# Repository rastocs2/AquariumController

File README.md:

AquariumController
==================

Aquarium controller based on Arduino and 4D Systems Intelligent Display Module.

## Components

1. Arduino Mega 2560 R3 (http://arduino.cc/en/Main/ArduinoBoardMega2560)
2. 4D Systems µLCD-28PTU (http://www.4dsystems.com.au/product/1/8/4D_Intelligent_Display_Modules/uLCD_28PTU/)
3. Real Time Clock Module DS3231 - it is much more accurate than DS1307 (http://www.ebay.com/sch/i.html?_trksid=p2050601.m570.l1313.TR0.TRC0.XDS3231+AT24C32&_nkw=DS3231+AT24C32&_sacat=0&_from=R40)
4. 8 Channel 5V Opto-Isolated Relay Module Shield (http://www.ebay.com/sch/i.html?_odkw=8+Channel+5V+Relay+Module&_osacat=0&_from=R40&_trksid=p2045573.m570.l1311.R1.TR3.TRC2.A0&_nkw=8+channel+5v+relay+module&_sacat=0)
5. Digital Temperature Sensor DS18B20 (http://www.ebay.com/sch/i.html?_odkw=DS18B20+Waterproof&_osacat=0&_from=R40&_trksid=p2045573.m570.l1311.R1.TR2.TRC1.A0.XDS18B20+aterproof&_nkw=ds18b20+waterproof&_sacat=0)
6. pH module based on LMP91200 (http://www.ti.com/product/lmp91200)
7. ORP module based on LMP91200 (http://www.ti.com/product/lmp91200)
8. WiFi module based on CC3000 (http://www.ti.com/product/cc3000) - will finished in version 3.0

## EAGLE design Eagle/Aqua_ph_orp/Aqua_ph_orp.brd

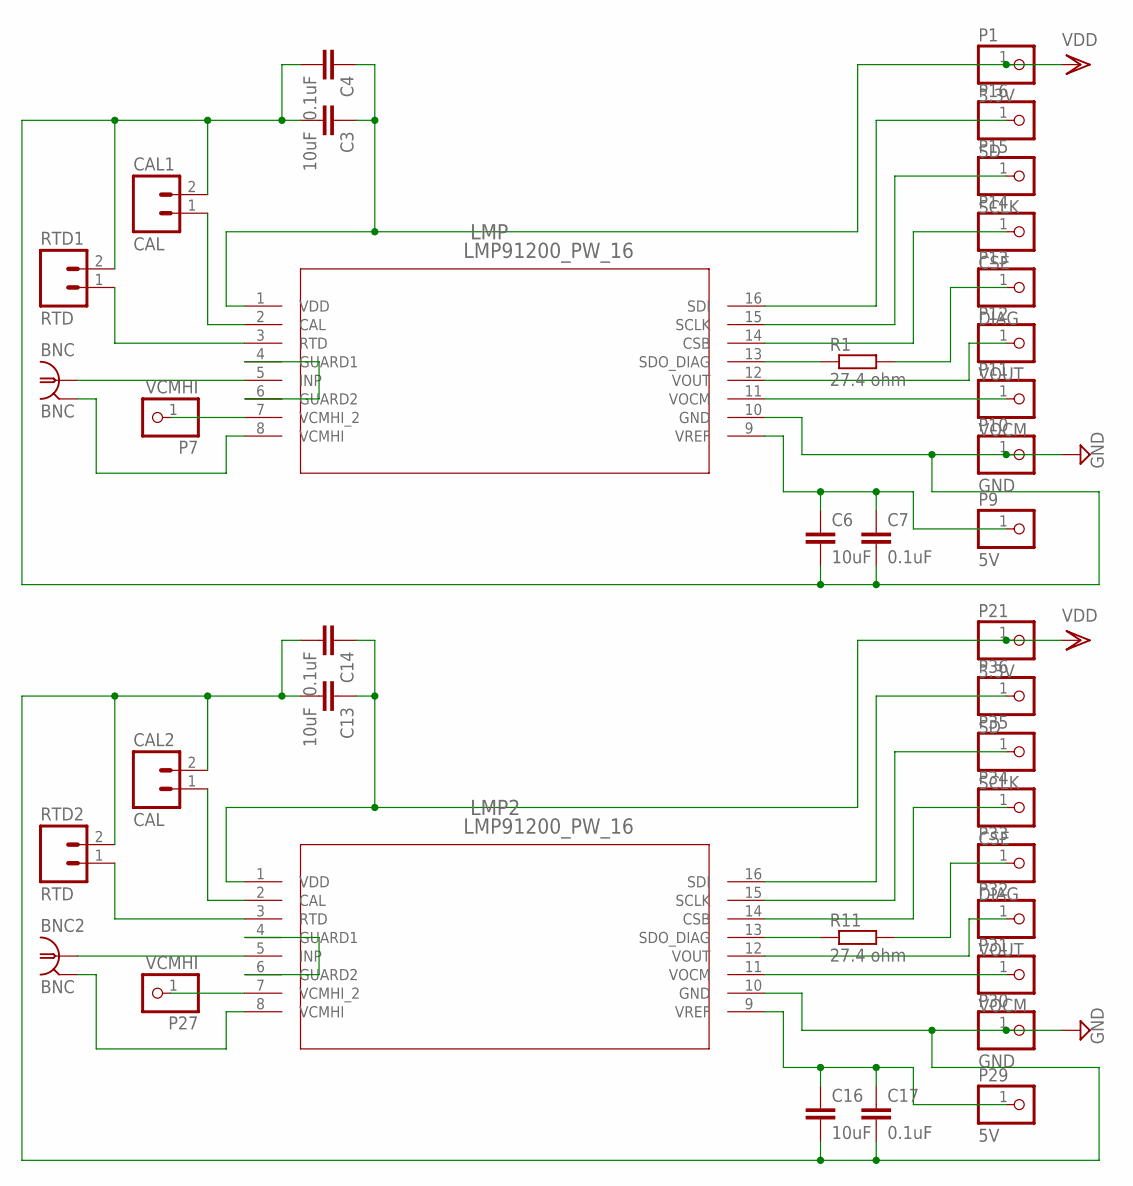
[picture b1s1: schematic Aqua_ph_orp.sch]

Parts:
BNC, BNC2: BNC; AMP_227161
C3, C6, C13, C16: 10uF; C3216
C4, C14: 0.1uF; C0603
C7, C17: 0.1uF; C1206
CAL1, CAL2: CAL; SCREWTERMINAL-KF-301-2P
LMP, LMP2: LMP91200_PW_16; MTC16
P1, P21: 3.3V; 1X01
P7, P27: VCMHI; 1X01
P9, P29: 5V; 1X01
P10, P30: GND; 1X01
P11, P31: VOCM; 1X01
P12, P32: VOUT; 1X01
P13, P33: DIAG; 1X01
P14, P34: CSE; 1X01
P15, P35: SCLK; 1X01
P16, P36: SD; 1X01
R1, R11: 27.4 ohm; R0603
RTD1, RTD2: RTD; SCREWTERMINAL-KF-301-2P

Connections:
GND: C3.2, C4.2, C6.2, C7.2, C13.2, C14.2, C16.2, C17.2, CAL1.2, CAL2.2, LMP.10 (GND), LMP2.10 (GND), P10.1, P30.1, RTD1.2, RTD2.2
unnamed: LMP.7 (VCMHI_2), P7.1
unnamed: BNC.2 (GND), LMP.8 (VCMHI)
unnamed: LMP.4 (GUARD1), LMP.6 (GUARD2)
unnamed: CAL1.1, LMP.2 (CAL)
unnamed: LMP.3 (RTD), RTD1.1
unnamed: C6.1, C7.1, LMP.9 (VREF), P9.1
unnamed: LMP2.14 (CSB), P34.1
unnamed: LMP2.15 (SCLK), P35.1
unnamed: LMP2.16 (SDI), P36.1
unnamed: LMP2.12 (VOUT), P32.1
unnamed: P33.1, R11.2
unnamed: LMP2.11 (VOCM), P31.1
unnamed: LMP2.13 (SDO_DIAG), R11.1
unnamed: BNC2.1, LMP2.5 (INP)
unnamed: LMP2.7 (VCMHI_2), P27.1
unnamed: BNC2.2 (GND), LMP2.8 (VCMHI)
unnamed: LMP2.4 (GUARD1), LMP2.6 (GUARD2)
unnamed: CAL2.1, LMP2.2 (CAL)
unnamed: LMP2.3 (RTD), RTD2.1
unnamed: C16.1, C17.1, LMP2.9 (VREF), P29.1
unnamed: LMP.14 (CSB), P14.1
unnamed: LMP.15 (SCLK), P15.1
unnamed: LMP.16 (SDI), P16.1
unnamed: LMP.12 (VOUT), P12.1
unnamed: P13.1, R1.2
unnamed: LMP.11 (VOCM), P11.1
unnamed: LMP.13 (SDO_DIAG), R1.1
unnamed: BNC.1, LMP.5 (INP)
VDD: C3.1, C4.1, C13.1, C14.1, LMP.1 (VDD), LMP2.1 (VDD), P1.1, P21.1

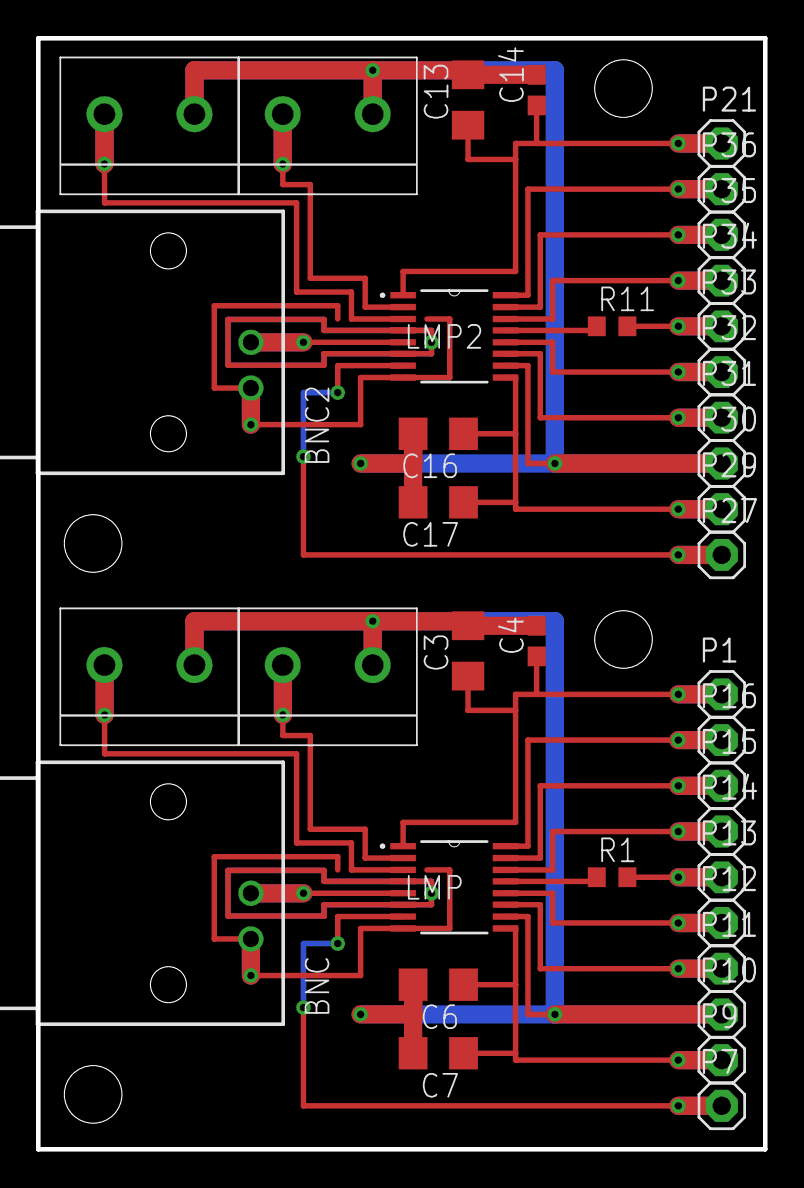
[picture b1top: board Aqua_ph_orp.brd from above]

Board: 2 copper layers, 40.4 x 61.7 mm, 38 parts (0 on the bottom side), 30 nets.

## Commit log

2013-11-24 Update LICENSE
2013-11-24 version 1.0 - Initial version without pH module and ORP module
2013-11-28 cleanup
2013-11-28 images
2013-12-30 support for DS3231
2014-01-02 version 1.2 - automatic Daylight Time Saving
2014-01-12 version 2.0 - added pH and ORP module
2014-02-21 small change in pH and ORP calculation for better accuracy
2014-02-24 new form for calibration process + cleanup
2014-03-03 changed VREF to 3.3V (for LMP91200 changed also VDD to 3.3V)
2014-04-01 fix in DST calculation
2014-04-08 adjustments in time settings + automatic calculation for day of week + chnages for new genieArduino library from 31.03.2014
2014-04-20 little adjustments in time library
2014-05-06 new image
2014-05-07 preparation for using ADC141S626 and ADS1115 in PH and ORP module

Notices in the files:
parts and their libraries:
SparkFun-Connectors: Licensing: CC v3.0 Share-Alike You are welcome to use this library for commercial purposes.
